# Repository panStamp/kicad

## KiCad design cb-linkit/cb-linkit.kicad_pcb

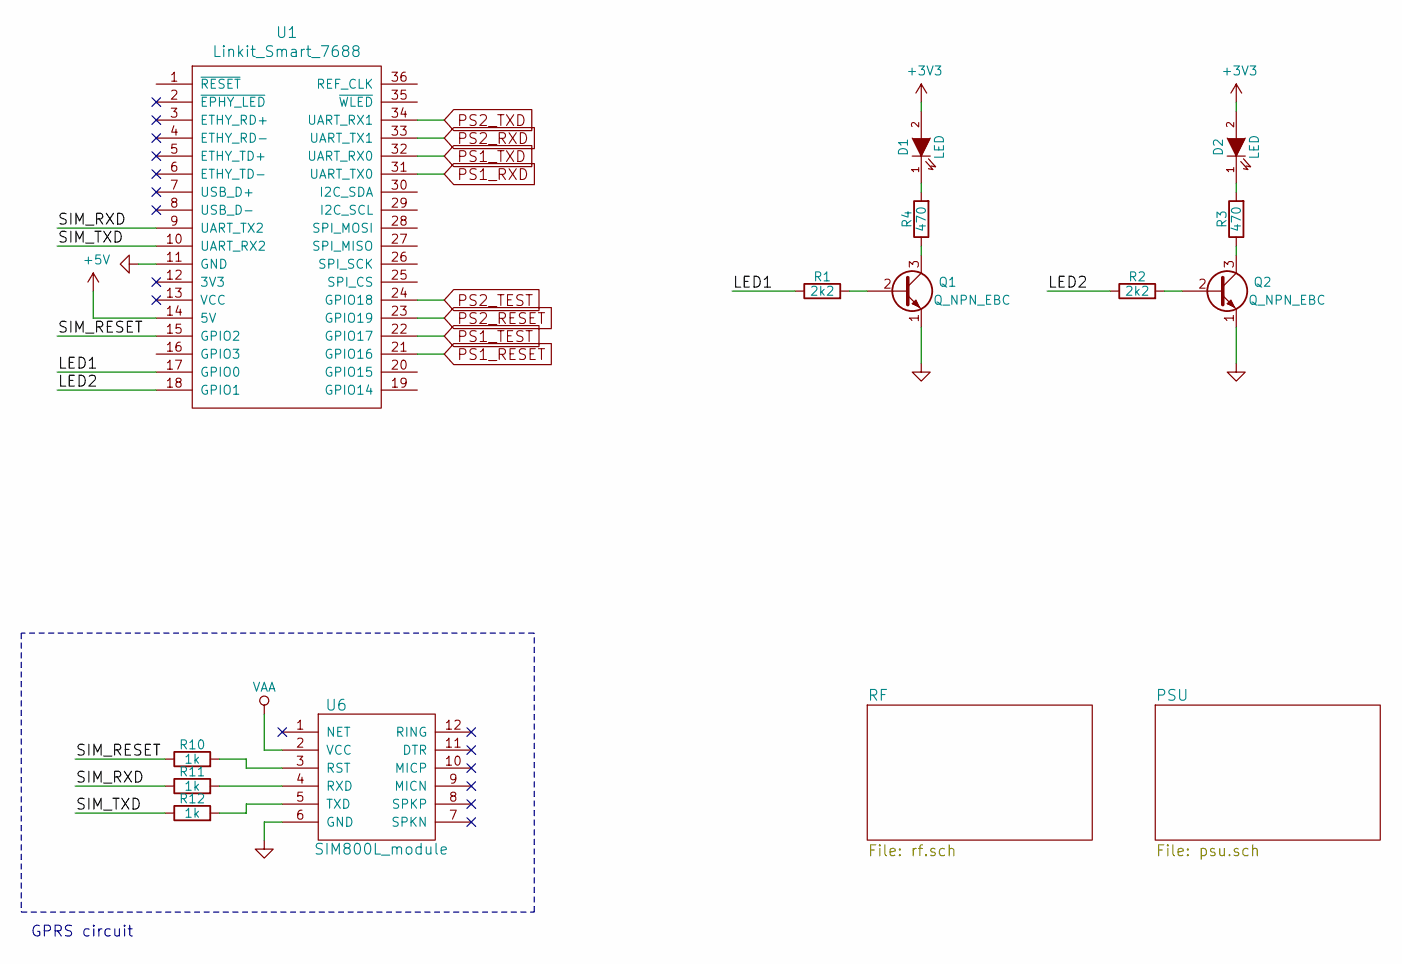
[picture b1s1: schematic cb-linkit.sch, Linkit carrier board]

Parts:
D1, D2: LED; SM0603S_POL
Q1, Q2: Q_NPN_EBC; SOT23EBC
R1, R2: 2k2; SM0603S
R3, R4: 470; SM0603S
R10, R11, R12: 1k; SM0603S
U1: Linkit_Smart_7688; DIP36-1
U6: SIM800L_module; SIM800L_MODULE

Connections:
+3V3: D1.2 (A), D2.2 (A); also elsewhere on the board
+5V: U1.14 (5V); also elsewhere on the board
/LED1: R1.1, U1.17 (GPIO0)
/LED2: R2.1, U1.18 (GPIO1)
/SIM_RESET: R10.1, U1.15 (GPIO2)
/SIM_RXD: R11.1, U1.9 (UART_TX2)
/SIM_TXD: R12.1, U1.10 (UART_RX2)
GND: Q1.1 (E), Q2.1 (E), U1.11 (GND), U6.6 (GND); also elsewhere on the board
unnamed: D1.1 (K), R4.2
unnamed: D2.1 (K), R3.2
unnamed: Q1.2 (B), R1.2
unnamed: Q1.3 (C), R4.1
unnamed: Q2.2 (B), R2.2
unnamed: Q2.3 (C), R3.1
unnamed: R10.2, U6.3 (RST)
unnamed: R11.2, U6.4 (RXD)
unnamed: R12.2, U6.5 (TXD)
PS1_RESET: U1.21 (GPIO16); also elsewhere on the board
PS1_RXD: U1.31 (UART_TX0); also elsewhere on the board
PS1_TEST: U1.22 (GPIO17); also elsewhere on the board
PS1_TXD: U1.32 (UART_RX0); also elsewhere on the board
PS2_RESET: U1.23 (GPIO19); also elsewhere on the board
PS2_RXD: U1.33 (UART_TX1); also elsewhere on the board
PS2_TEST: U1.24 (GPIO18); also elsewhere on the board
PS2_TXD: U1.34 (UART_RX1); also elsewhere on the board
VAA: U6.2 (VCC); also elsewhere on the board

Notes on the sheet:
GPRS circuit

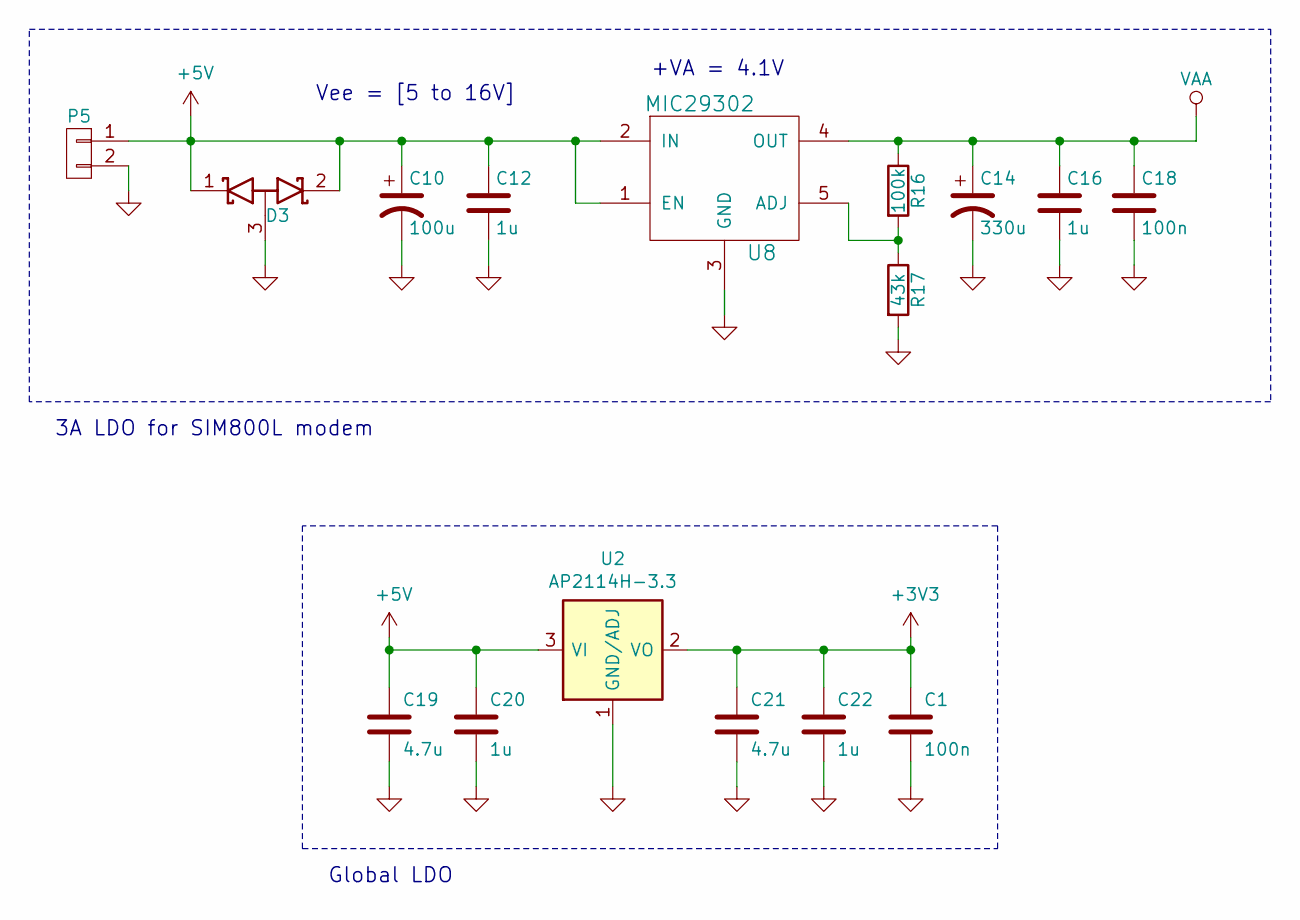
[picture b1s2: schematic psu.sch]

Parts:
C1, C18: 100n; SM0603S
C10: 100u; SMDCPOL_6.3
C12, C16, C20, C22: 1u; SM0603S
C14: 330u; SMDCPOL_8
C19, C21: 4.7u; SM0603S
D3: D_Schottky_x2_ACom_KKA; SOT23
P5: CONN_01X02; PWR_3A
R16: 100k; SM0603S
R17: 43k; SM0603S
U2: AP2114H-3.3; SOT223
U8: MIC29302; TO-252

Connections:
+3V3: C1.1, C21.1, C22.1, U2.2 (VO); also elsewhere on the board
+5V: C10.1, C12.1, C19.1, C20.1, D3.1 (K), D3.2 (K), P5.1, U2.3 (VI), U8.1 (EN), U8.2 (IN); also elsewhere on the board
GND: C1.2, C10.2, C12.2, C14.2, C16.2, C18.2, C19.2, C20.2, C21.2, C22.2, D3.3 (A), P5.2, R17.2, U2.1 (GND/ADJ), U8.3 (GND); also elsewhere on the board
unnamed: R16.2, R17.1, U8.5 (ADJ)
VAA: C14.1, C16.1, C18.1, R16.1, U8.4 (OUT); also elsewhere on the board

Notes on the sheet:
+VA = 4.1V
Vee = [5 to 16V]
3A LDO for SIM800L modem
Global LDO

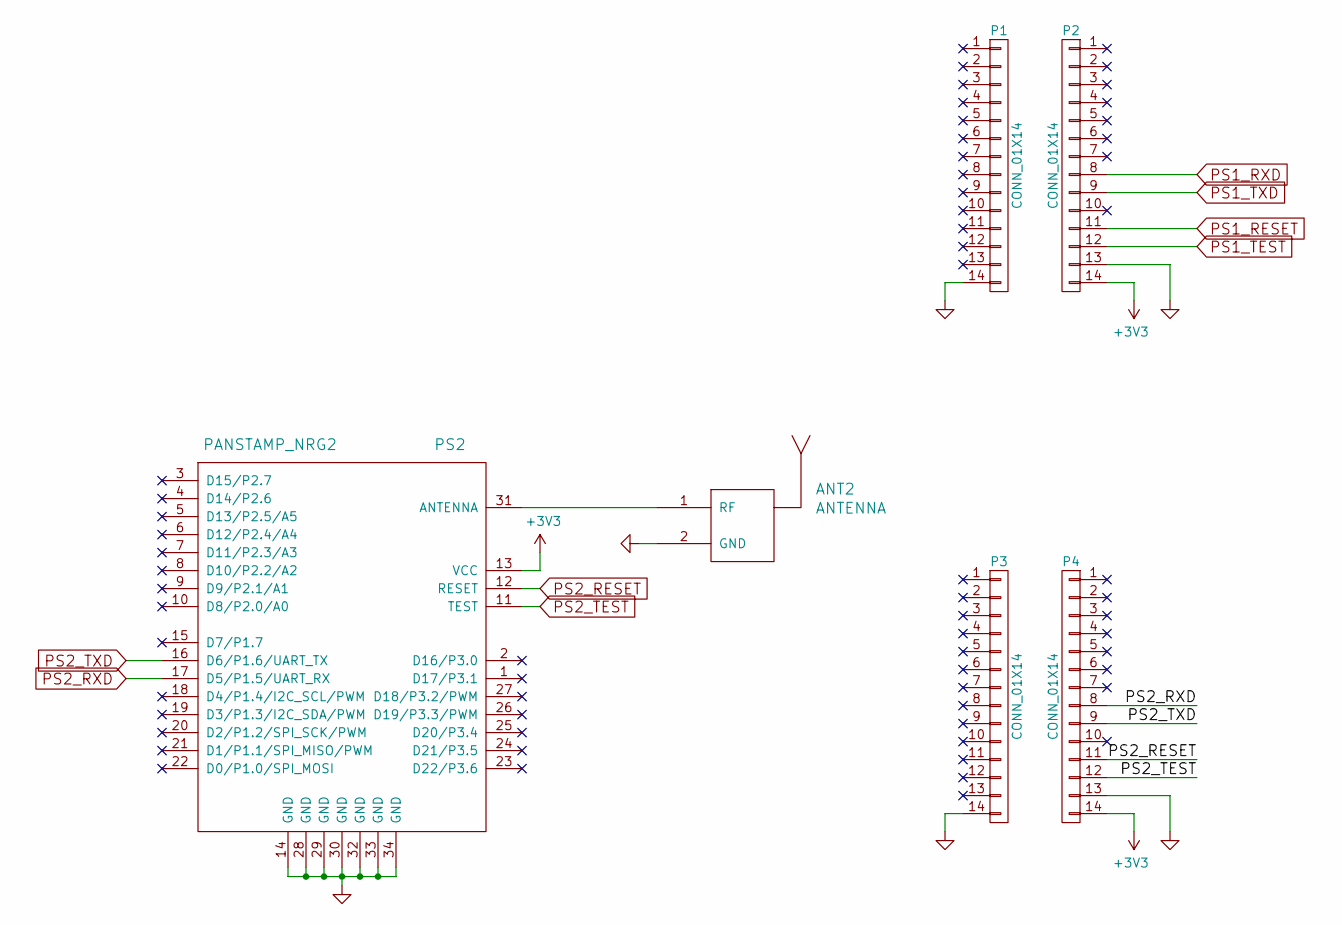
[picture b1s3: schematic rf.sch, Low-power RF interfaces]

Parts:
ANT2: ANTENNA; SMA_RightAngle_Tyco
P1, P2, P3, P4: CONN_01X14; Pin_Header_Straight_1x14
PS2: PANSTAMP_NRG2; PANSTAMP_2

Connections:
+3V3: P2.14, P4.14, PS2.13 (VCC); also elsewhere on the board
GND: ANT2.2 (GND), P1.14, P2.13, P3.14, P4.13, PS2.14 (GND), PS2.28 (GND), PS2.29 (GND), PS2.30 (GND), PS2.32 (GND), PS2.33 (GND), PS2.34 (GND); also elsewhere on the board
unnamed: ANT2.1 (RF), PS2.31 (ANTENNA)
PS1_RESET: P2.11; also elsewhere on the board
PS1_RXD: P2.8; also elsewhere on the board
PS1_TEST: P2.12; also elsewhere on the board
PS1_TXD: P2.9; also elsewhere on the board
PS2_RESET: P4.11, PS2.12 (RESET); also elsewhere on the board
PS2_RXD: P4.8, PS2.17 (D5/P1.5/UART_RX); also elsewhere on the board
PS2_TEST: P4.12, PS2.11 (TEST); also elsewhere on the board
PS2_TXD: P4.9, PS2.16 (D6/P1.6/UART_TX); also elsewhere on the board

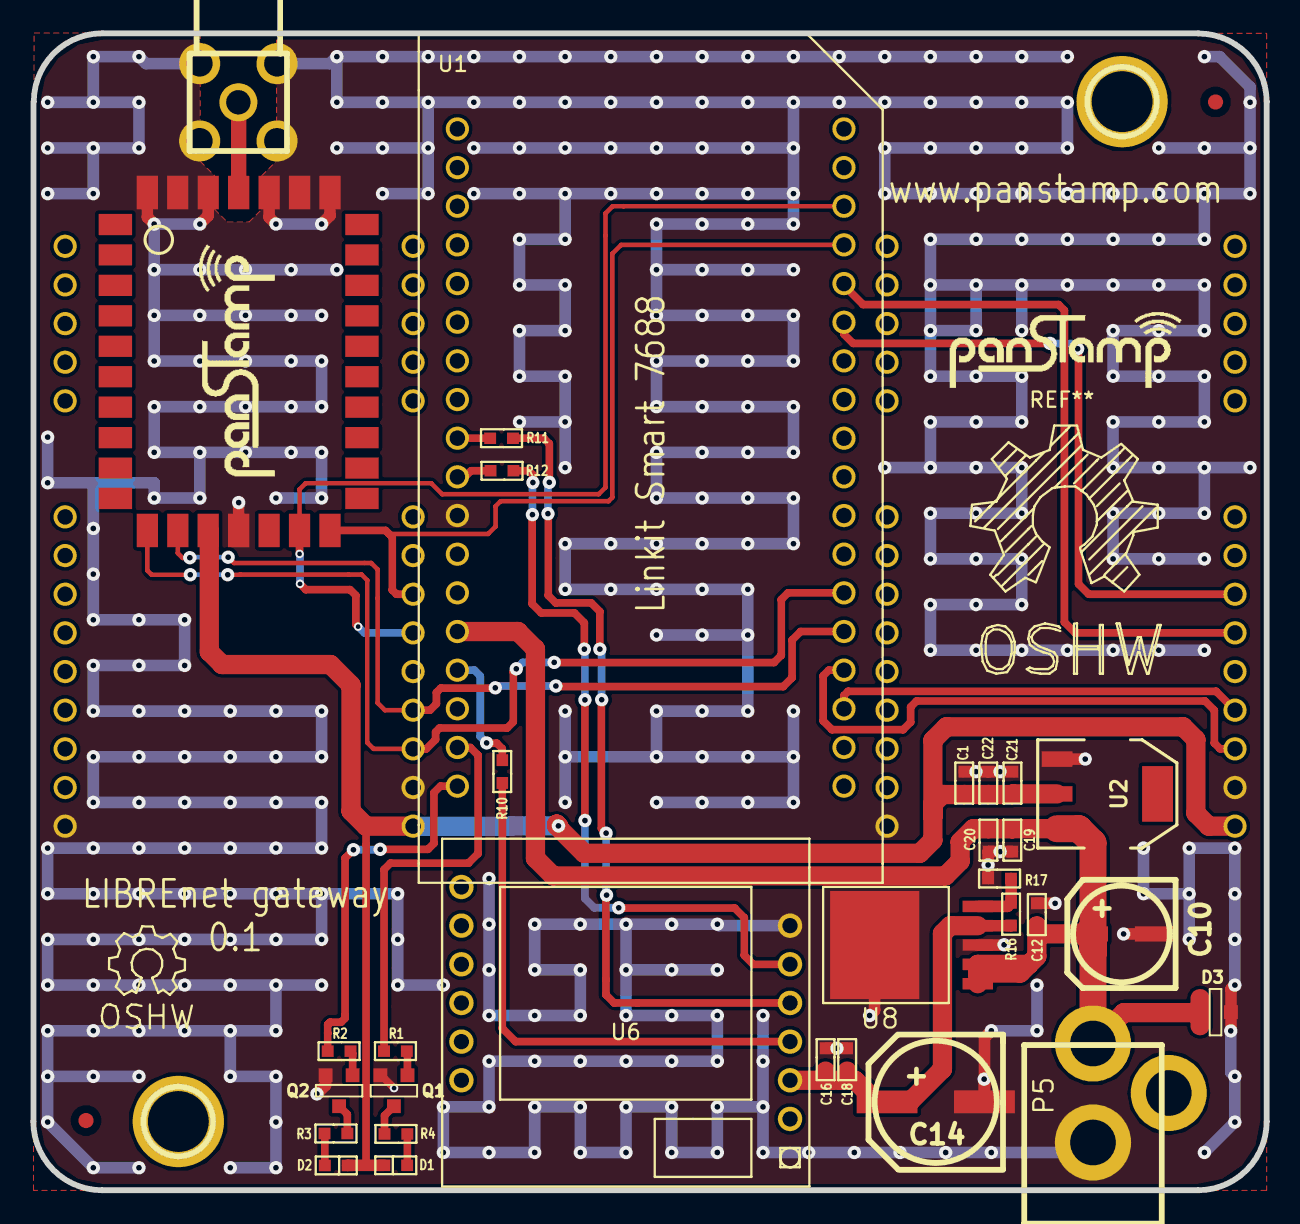
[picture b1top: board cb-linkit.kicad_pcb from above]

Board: 4 copper layers, 81.0 x 76.0 mm, 39 parts (0 on the bottom side), 28 nets.

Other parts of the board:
1PIN, 1PIN#2: P***; 1pin
fiducial: VAL**; fiducial
fiducial#2: VAL**; fiducial

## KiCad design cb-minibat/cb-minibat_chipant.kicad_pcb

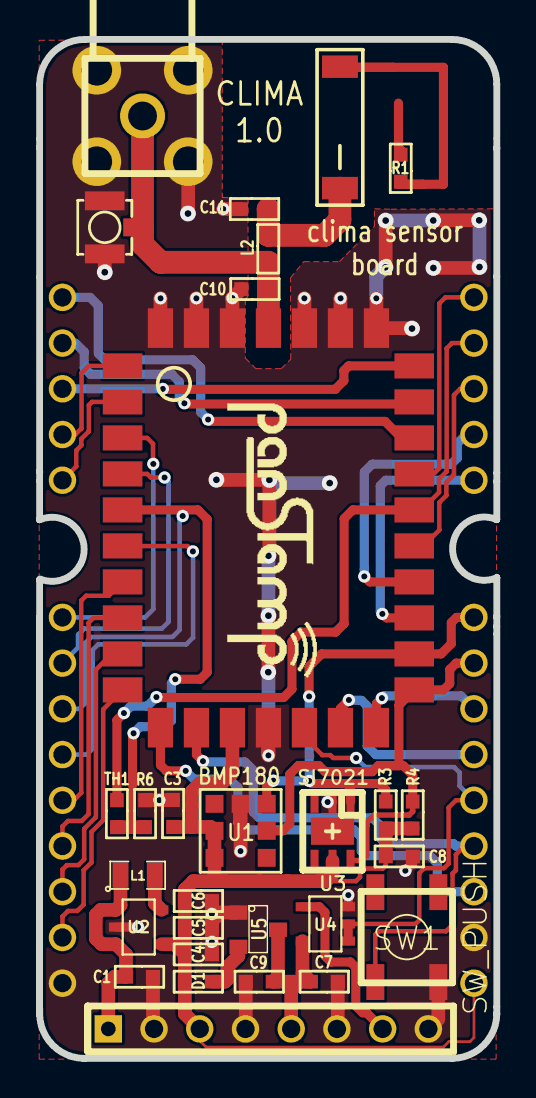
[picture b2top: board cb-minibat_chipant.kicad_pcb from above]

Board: 4 copper layers, 25.4 x 56.6 mm, 31 parts (0 on the bottom side), 35 nets.

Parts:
ANT1: ANTENNA; SMA_RightAngle_Tyco
ANT2: ANTENNA; U.FL_CONN
C1, C4, C9: 10u; SM0603S
C3, C6, C7, C8: 100n; SM0603S
C5: 1u; SM0603S
C10: 3.9p; SM0603S
C11: 0.3p; SM0603S
D1: SD0603S040S0R2; SM0603S
L1: 4.7u; SM0805
L2: 18n; SM0603S
L3: ANTENNA; 0868AT43A0020
P1, P2: CONN_01X14; pin_array_1x14
P3: CONN_8; PIN_ARRAY_8X1
PS1: PANSTAMP_NRG2; PANSTAMP_2
R1: 0; SM0603S
R3, R4, R6: 10k; SM0603S
SW1: SW_PUSH; switch-tact-noah
TH1: THERMISTOR; SM0603S
U1: BMP180
U2: MAX1724; SOT23-5
U3: SI7021; DFN-6
U4: M74VHC1GT08; SOT23-5
U5: MCP1702; SOT23

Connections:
+5V: C7.1, C9.1, P3.5, U4.5, U5.3
+BATT: C1.1, L1.1, P3.1, U2.1, U2.3
/5VOUT: P3.7, U4.4
/A5: P1.8, PS1.5, R6.1, TH1.1
/CHIP_ANT: C11.1, L2.2, L3.1
/D0: P2.3, PS1.22
/D1: P2.4, PS1.21
/D2: P2.5, PS1.20
/D5: P2.8, PS1.17
/D6: P2.9, PS1.16
/D7: P2.10, PS1.15, U4.1, U4.2
/D8: P1.13, PS1.10
/D9: P1.12, PS1.9
/D10: P1.11, PS1.8
/D11: P1.10, PS1.7
/D12: P1.9, PS1.6
/D14: P1.7, PS1.4
/D15: P1.6, PS1.3
/D16: P1.5, PS1.2
/D17: P1.4, PS1.1
/D18: P1.3, PS1.27
/D19: P1.2, PS1.26
/D20: P1.1, PS1.25
/D21: P2.1, PS1.24
/D22: P2.2, PS1.23, TH1.2
/I2C_SCL: P2.7, PS1.18, R4.2, U1.5, U3.6
/I2C_SDA: P2.6, PS1.19, R3.2, U1.6, U3.1
/RESET: P2.11, PS1.12, SW1.1
/TEST: P2.12, PS1.11
/TOANT: ANT1.1, ANT2.1, C10.1, L2.1, PS1.31
GND: ANT1.2, ANT2.2, C1.2, C3.2, C4.2, C5.2, C6.2, C7.2, C8.2, C9.2, C10.2, C11.2, P1.14, P2.13, P3.2, P3.4, P3.6, P3.8, PS1.14, PS1.28, PS1.29, PS1.30, PS1.32, PS1.33, PS1.34, R6.2, SW1.2, U1.7, U2.2, U3.2, U4.3, U5.1
unnamed: D1.1, U5.2
unnamed: L1.2, U2.5
unnamed: L3.2, R1.2
VCC: C3.1, C4.1, C5.1, C6.1, C8.1, D1.2, P2.14, P3.3, PS1.13, R3.1, R4.1, U1.2, U1.3, U2.4, U3.5

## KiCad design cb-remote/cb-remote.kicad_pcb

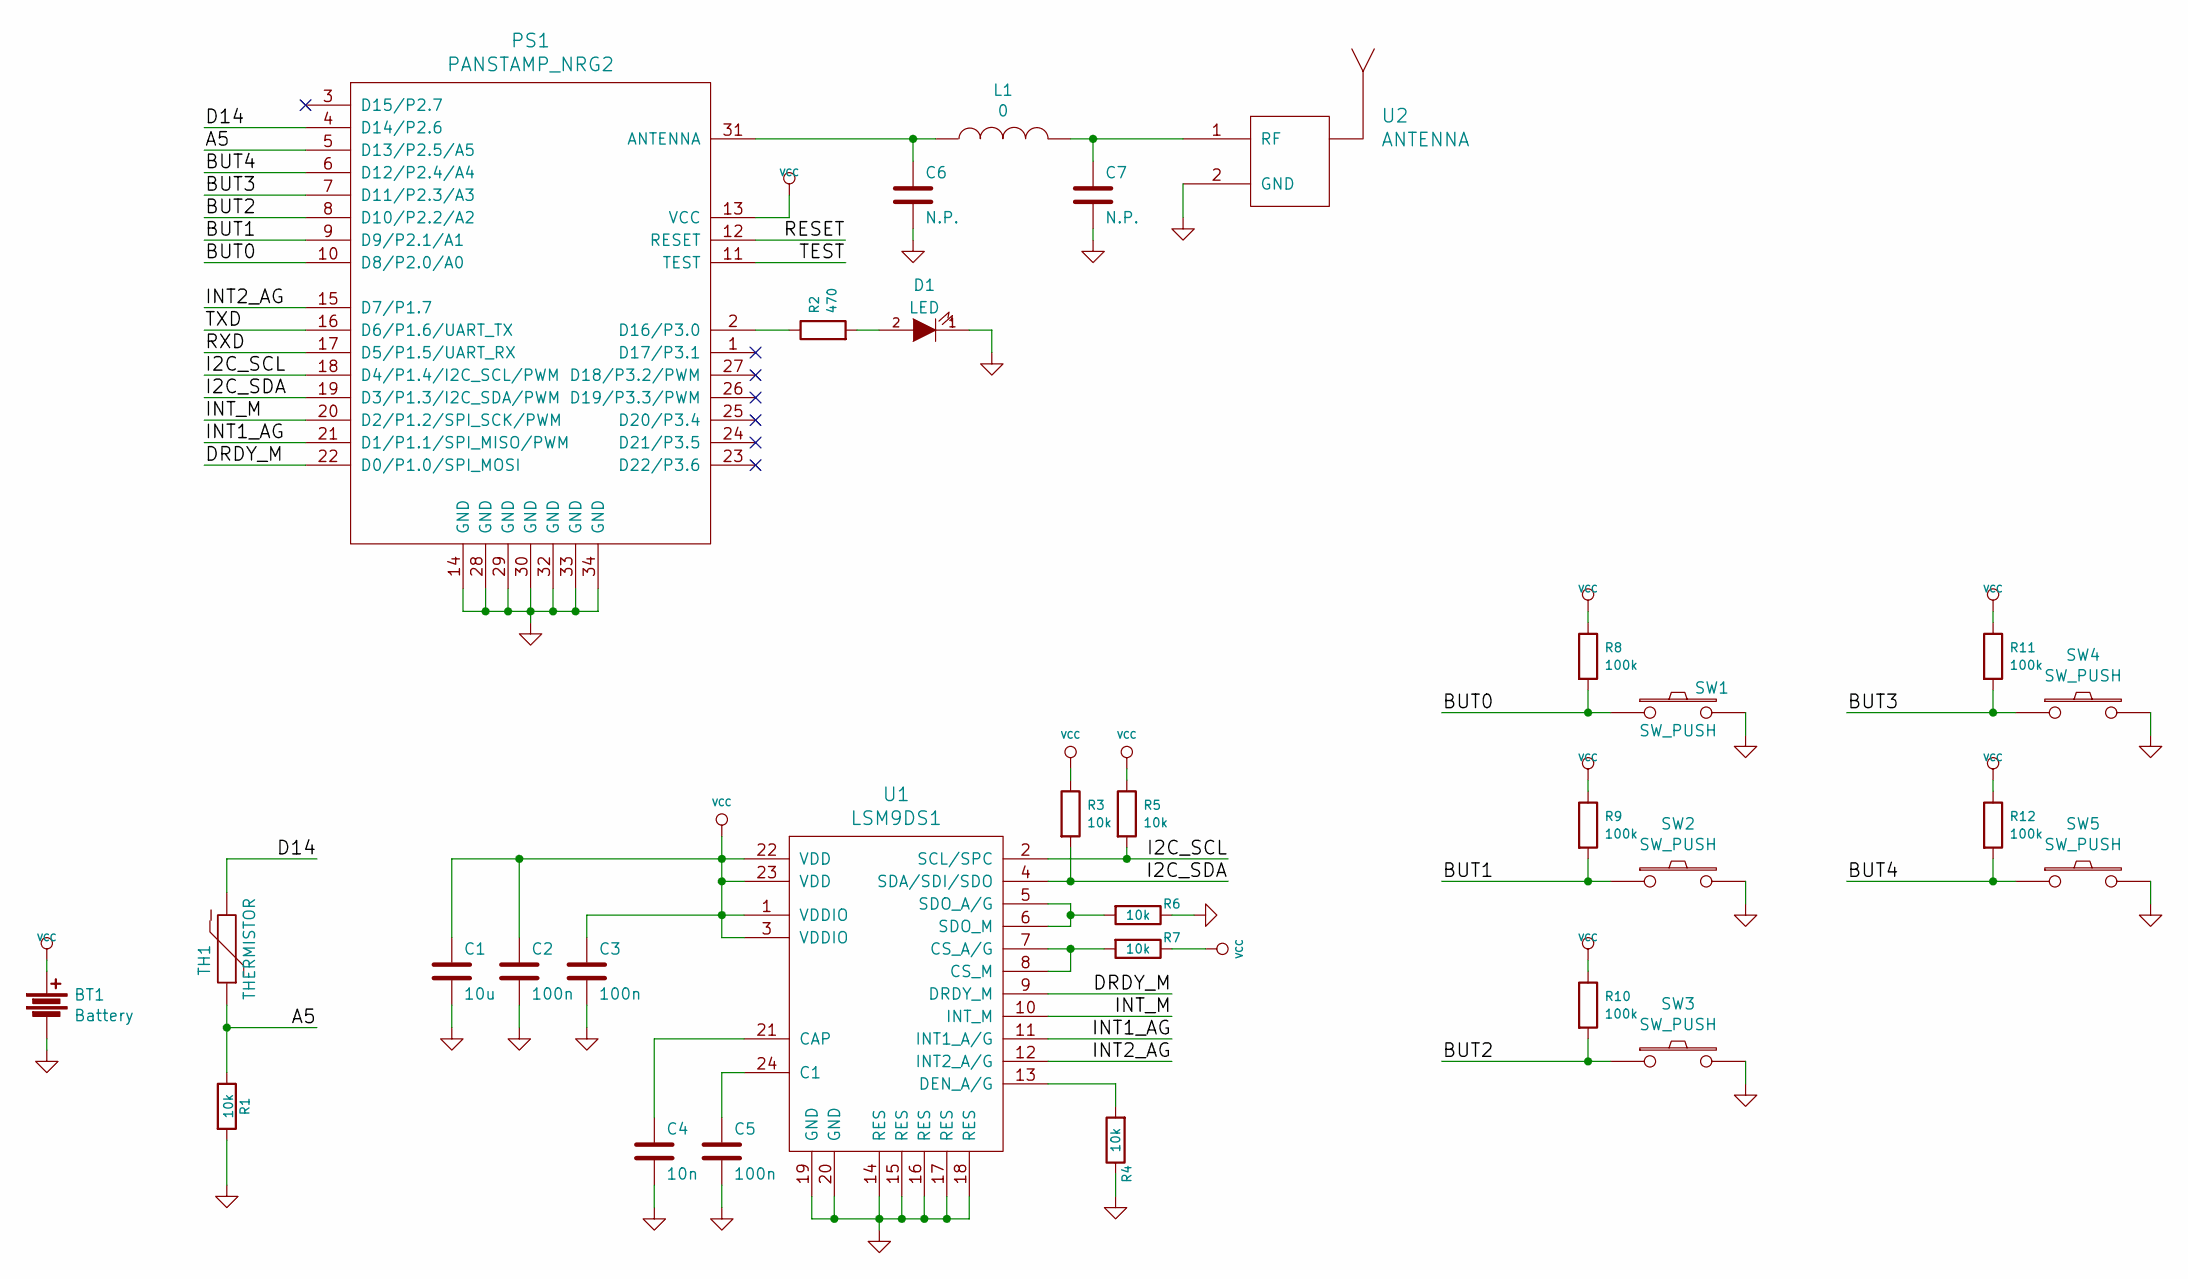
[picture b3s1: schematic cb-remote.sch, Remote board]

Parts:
BT1: Battery; linx_bat-hld-001
C1: 10u; SM0603S
C2, C3, C5: 100n; SM0603S
C4: 10n; SM0603S
C6, C7: N.P.; SM0603S
D1: LED; SM0603_POL
L1: 0; SM0603S
PS1: PANSTAMP_NRG2; PANSTAMP_2
R1, R3, R4, R5, R6, R7: 10k; SM0603S
R2: 470; SM0603S
R8, R9, R10, R11, R12: 100k; SM0603S
SW1, SW2, SW3, SW4, SW5: SW_PUSH; minimum_jumper
TH1: THERMISTOR; SM0603S
U1: LSM9DS1; LGA24L
U2: ANTENNA; U.FL_CONN

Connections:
/A5: PS1.5 (D13/P2.5/A5), R1.1, TH1.1
/BUT0: PS1.10 (D8/P2.0/A0), R8.2, SW1.1
/BUT1: PS1.9 (D9/P2.1/A1), R9.2, SW2.1
/BUT2: PS1.8 (D10/P2.2/A2), R10.2, SW3.1
/BUT3: PS1.7 (D11/P2.3/A3), R11.2, SW4.1
/BUT4: PS1.6 (D12/P2.4/A4), R12.2, SW5.1
/D14: PS1.4 (D14/P2.6), TH1.2
/DRDY_M: PS1.22 (D0/P1.0/SPI_MOSI), U1.9 (DRDY_M)
/I2C_SCL: PS1.18 (D4/P1.4/I2C_SCL/PWM), R5.2, U1.2 (SCL/SPC)
/I2C_SDA: PS1.19 (D3/P1.3/I2C_SDA/PWM), R3.2, U1.4 (SDA/SDI/SDO)
/INT1_AG: PS1.21 (D1/P1.1/SPI_MISO/PWM), U1.11 (INT1_A/G)
/INT2_AG: PS1.15 (D7/P1.7), U1.12 (INT2_A/G)
/INT_M: PS1.20 (D2/P1.2/SPI_SCK/PWM), U1.10 (INT_M)
/RESET: PS1.12 (RESET)
/RXD: PS1.17 (D5/P1.5/UART_RX)
/TEST: PS1.11 (TEST)
/TXD: PS1.16 (D6/P1.6/UART_TX)
GND: BT1.2, C1.2, C2.2, C3.2, C4.2, C5.2, C6.2, C7.2, D1.1 (K), PS1.14 (GND), PS1.28 (GND), PS1.29 (GND), PS1.30 (GND), PS1.32 (GND), PS1.33 (GND), PS1.34 (GND), R1.2, R4.1, R6.1, SW1.2, SW2.2, SW3.2, SW4.2, SW5.2, U1.14 (RES), U1.15 (RES), U1.16 (RES), U1.17 (RES), U1.18 (RES), U1.19 (GND), U1.20 (GND), U2.2 (GND)
unnamed: C4.1, U1.21 (CAP)
unnamed: C5.1, U1.24 (C1)
unnamed: C6.1, L1.1, PS1.31 (ANTENNA)
unnamed: C7.1, L1.2, U2.1 (RF)
unnamed: D1.2 (A), R2.2
unnamed: PS1.2 (D16/P3.0), R2.1
unnamed: R4.2, U1.13 (DEN_A/G)
unnamed: R6.2, U1.5 (SDO_A/G), U1.6 (SDO_M)
unnamed: R7.2, U1.7 (CS_A/G), U1.8 (CS_M)
VCC: BT1.1, C1.1, C2.1, C3.1, PS1.13 (VCC), R3.1, R5.1, R7.1, R8.1, R9.1, R10.1, R11.1, R12.1, U1.1 (VDDIO), U1.3 (VDDIO), U1.22 (VDD), U1.23 (VDD)

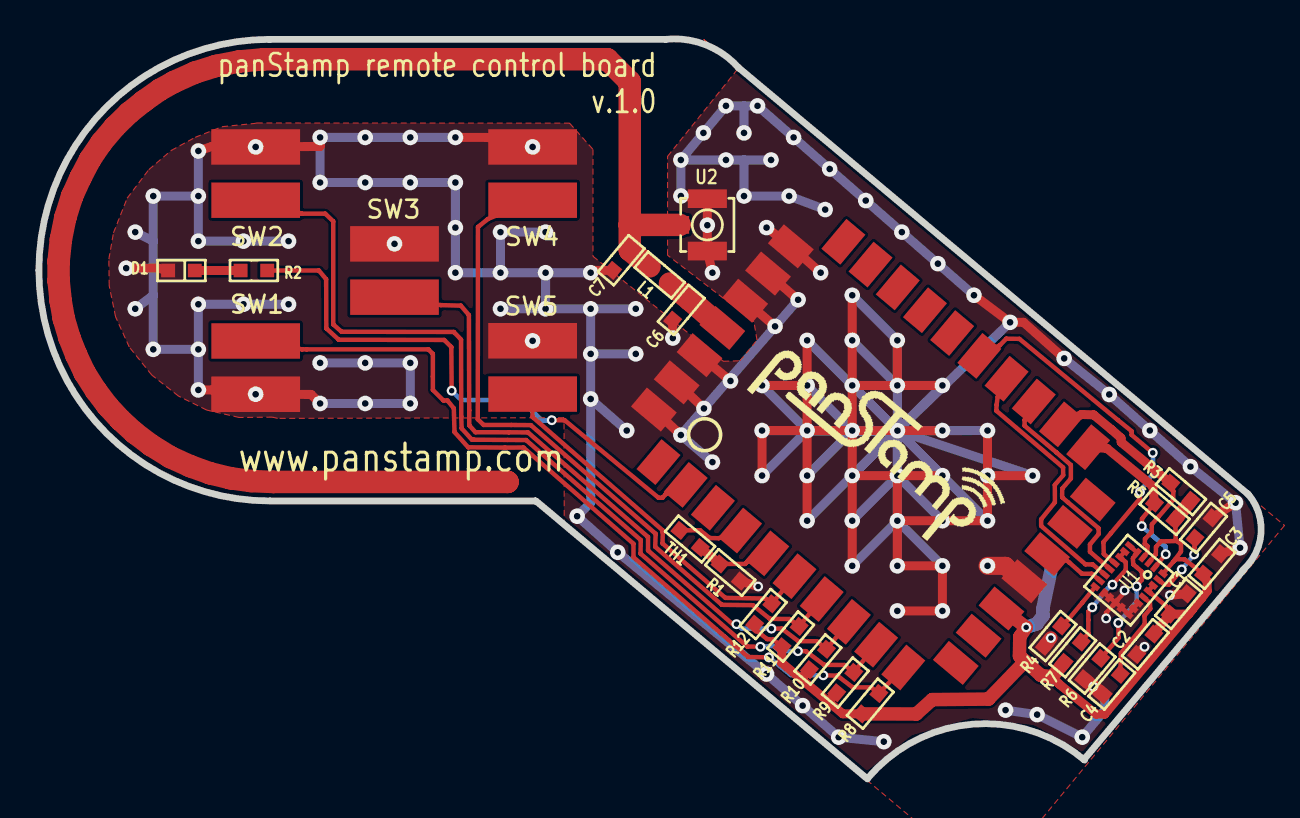
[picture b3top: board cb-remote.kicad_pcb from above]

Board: 4 copper layers, 68.8 x 41.7 mm, 31 parts (1 on the bottom side), 24 nets.

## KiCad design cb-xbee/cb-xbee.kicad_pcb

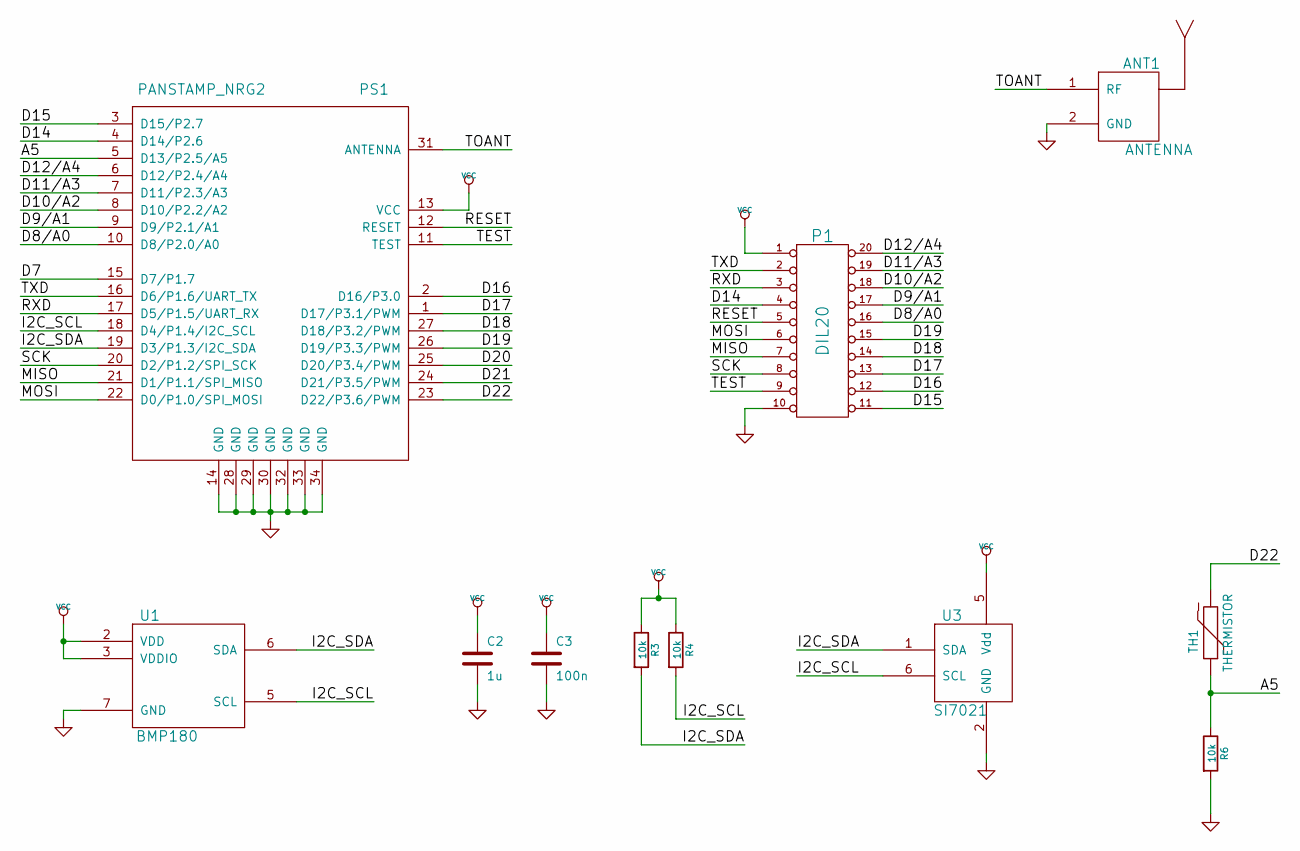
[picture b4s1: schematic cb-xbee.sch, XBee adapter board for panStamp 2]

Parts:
ANT1: ANTENNA; SMA_RightAngle_Tyco
C2: 1u; SM0603S
C3: 100n; SM0603S
P1: DIL20
PS1: PANSTAMP_NRG2; PANSTAMP_2
R3, R4, R6: 10k; SM0603S
TH1: THERMISTOR; SM0603S
U1: BMP180
U3: SI7021; DFN-6

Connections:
/A5: PS1.5 (D13/P2.5/A5), R6.1, TH1.1
/D7: PS1.15 (D7/P1.7)
/D8/A0: P1.16, PS1.10 (D8/P2.0/A0)
/D9/A1: P1.17, PS1.9 (D9/P2.1/A1)
/D10/A2: P1.18, PS1.8 (D10/P2.2/A2)
/D11/A3: P1.19, PS1.7 (D11/P2.3/A3)
/D12/A4: P1.20, PS1.6 (D12/P2.4/A4)
/D14: P1.4, PS1.4 (D14/P2.6)
/D15: P1.11, PS1.3 (D15/P2.7)
/D16: P1.12, PS1.2 (D16/P3.0)
/D17: P1.13, PS1.1 (D17/P3.1/PWM)
/D18: P1.14, PS1.27 (D18/P3.2/PWM)
/D19: P1.15, PS1.26 (D19/P3.3/PWM)
/D20: PS1.25 (D20/P3.4/PWM)
/D21: PS1.24 (D21/P3.5/PWM)
/D22: PS1.23 (D22/P3.6/PWM), TH1.2
/I2C_SCL: PS1.18 (D4/P1.4/I2C_SCL), R4.2, U1.5 (SCL), U3.6 (SCL)
/I2C_SDA: PS1.19 (D3/P1.3/I2C_SDA), R3.2, U1.6 (SDA), U3.1 (SDA)
/MISO: P1.7, PS1.21 (D1/P1.1/SPI_MISO)
/MOSI: P1.6, PS1.22 (D0/P1.0/SPI_MOSI)
/RESET: P1.5, PS1.12 (RESET)
/RXD: P1.3, PS1.17 (D5/P1.5/UART_RX)
/SCK: P1.8, PS1.20 (D2/P1.2/SPI_SCK)
/TEST: P1.9, PS1.11 (TEST)
/TOANT: ANT1.1 (RF), PS1.31 (ANTENNA)
/TXD: P1.2, PS1.16 (D6/P1.6/UART_TX)
GND: ANT1.2 (GND), C2.2, C3.2, P1.10, PS1.14 (GND), PS1.28 (GND), PS1.29 (GND), PS1.30 (GND), PS1.32 (GND), PS1.33 (GND), PS1.34 (GND), R6.2, U1.7 (GND), U3.2 (GND)
VCC: C2.1, C3.1, P1.1, PS1.13 (VCC), R3.1, R4.1, U1.2 (VDD), U1.3 (VDDIO), U3.5 (Vdd)

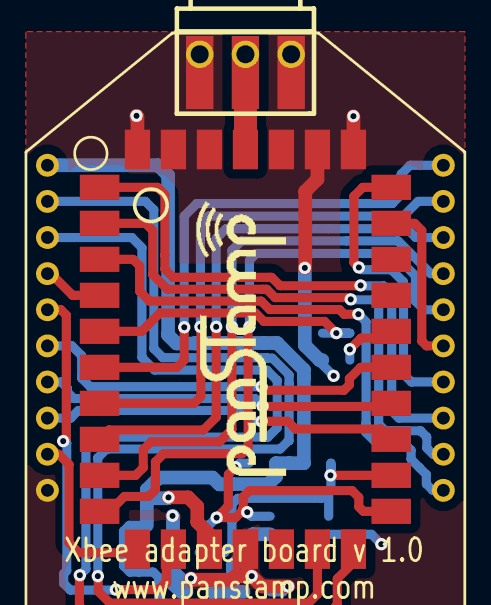
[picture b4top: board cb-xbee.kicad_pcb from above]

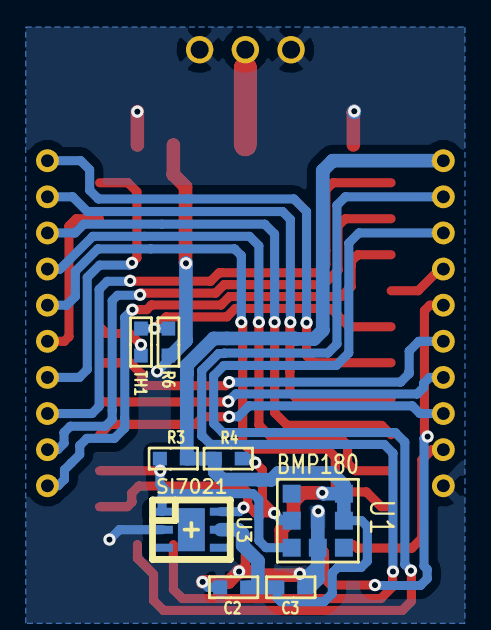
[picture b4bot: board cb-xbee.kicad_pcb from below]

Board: 4 copper layers, 11 parts (8 on the bottom side), 25 nets.

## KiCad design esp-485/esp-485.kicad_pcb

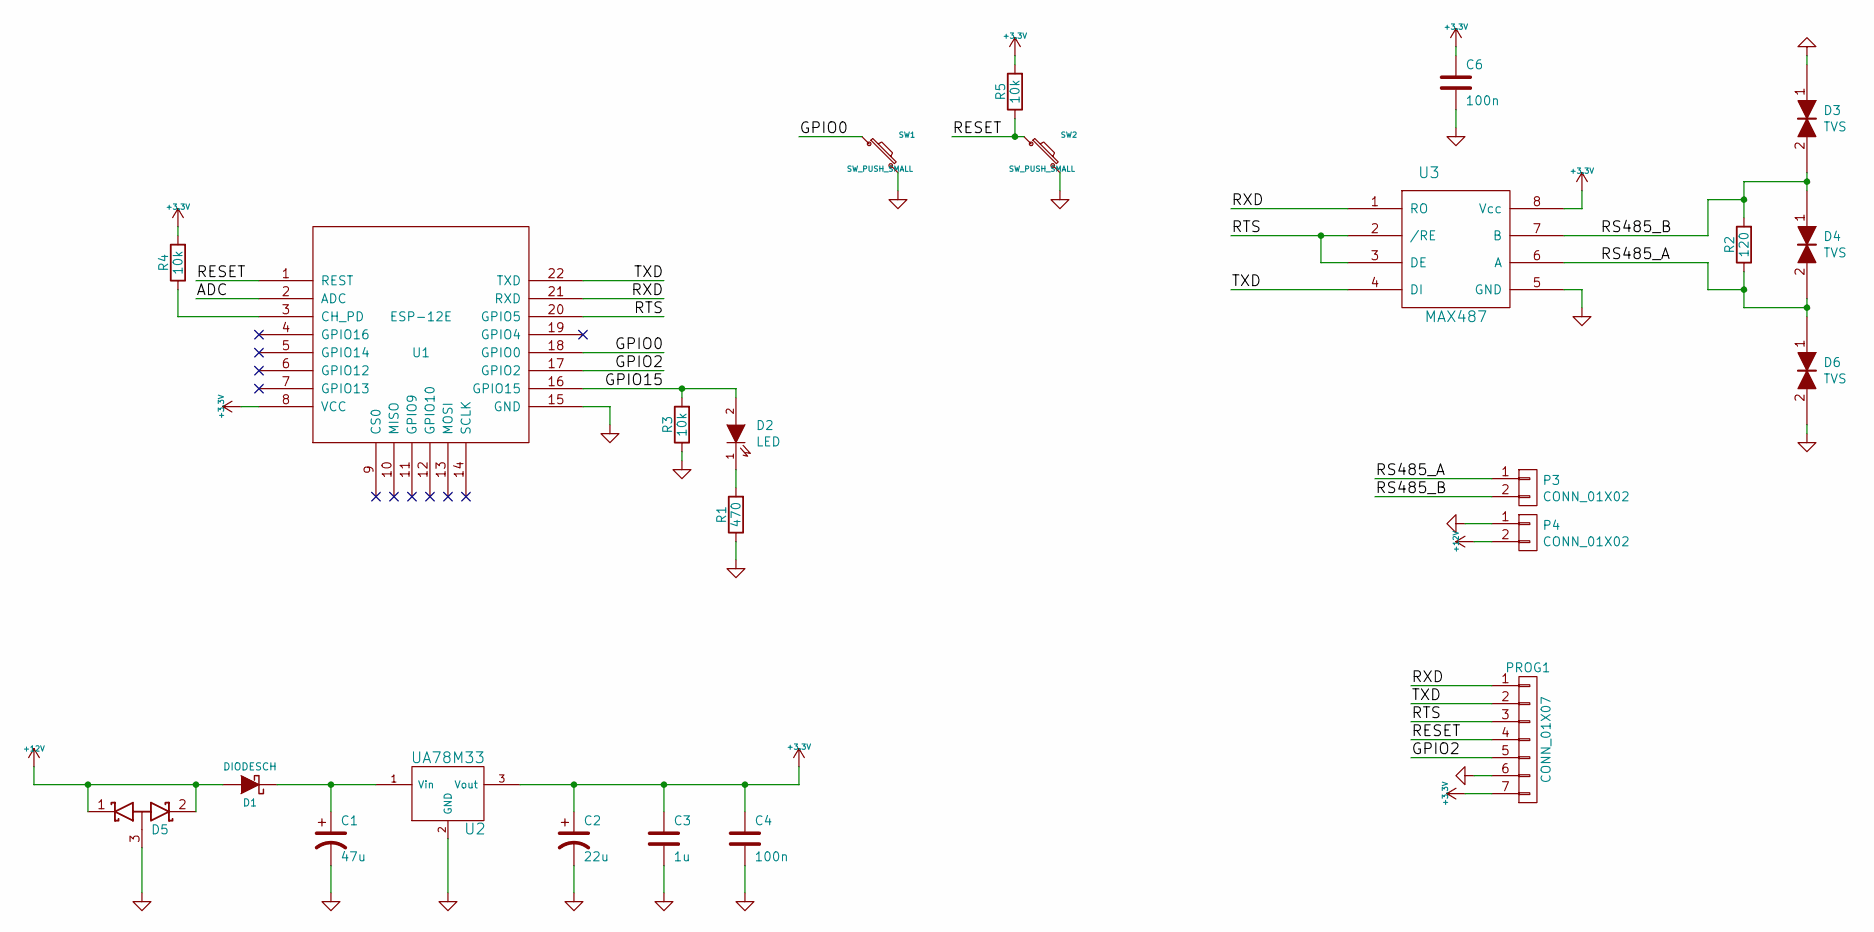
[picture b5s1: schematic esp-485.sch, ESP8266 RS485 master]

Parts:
C1: 47u; SMDCPOL_6.3
C2: 22u; SMDCPOL_5
C3: 1u; SM0603S
C4, C6: 100n; SM0603S
D1: DIODESCH; SMA
D2: LED; SM0603S_POL
D3, D4, D6: TVS; SOD-923
D5: D_Schottky_x2_ACom_KKA; SOT23
P3, P4: CONN_01X02; terminal_block_5mm_2P
PROG1: CONN_01X07; Pin_Header_Straight_1x07
R1: 470; SM0603S
R2: 120; SM0603S
R3, R4, R5: 10k; SM0603S
SW1, SW2: SW_PUSH_SMALL; switch-tact-noah
U1: ESP-12E
U2: UA78M33; SOT223
U3: MAX487; SO8E

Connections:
+3V3: C2.1, C3.1, C4.1, C6.1, PROG1.7, R4.2, R5.2, U1.8 (VCC), U2.3 (Vout), U3.8 (Vcc)
+12V: D1.2 (A), D5.1 (K), D5.2 (K), P4.2
/ADC: U1.2 (ADC)
/GPIO0: SW1.1, U1.18 (GPIO0)
/GPIO2: PROG1.5, U1.17 (GPIO2)
/GPIO15: D2.2 (A), R3.2, U1.16 (GPIO15)
/RESET: PROG1.4, R5.1, SW2.1, U1.1 (REST)
/RS485_A: D4.2, D6.1, P3.1, R2.1, U3.6 (A)
/RS485_B: D3.2, D4.1, P3.2, R2.2, U3.7 (B)
/RTS: PROG1.3, U1.20 (GPIO5), U3.2 (/RE), U3.3 (DE)
/RXD: PROG1.1, U1.21 (RXD), U3.1 (RO)
/TXD: PROG1.2, U1.22 (TXD), U3.4 (DI)
GND: C1.2, C2.2, C3.2, C4.2, C6.2, D3.1, D5.3 (A), D6.2, P4.1, PROG1.6, R1.1, R3.1, SW1.2, SW2.2, U1.15 (GND), U2.2 (GND), U2.4, U3.5 (GND)
unnamed: C1.1, D1.1 (K), U2.1 (Vin)
unnamed: D2.1 (K), R1.2
unnamed: R4.1, U1.3 (CH_PD)

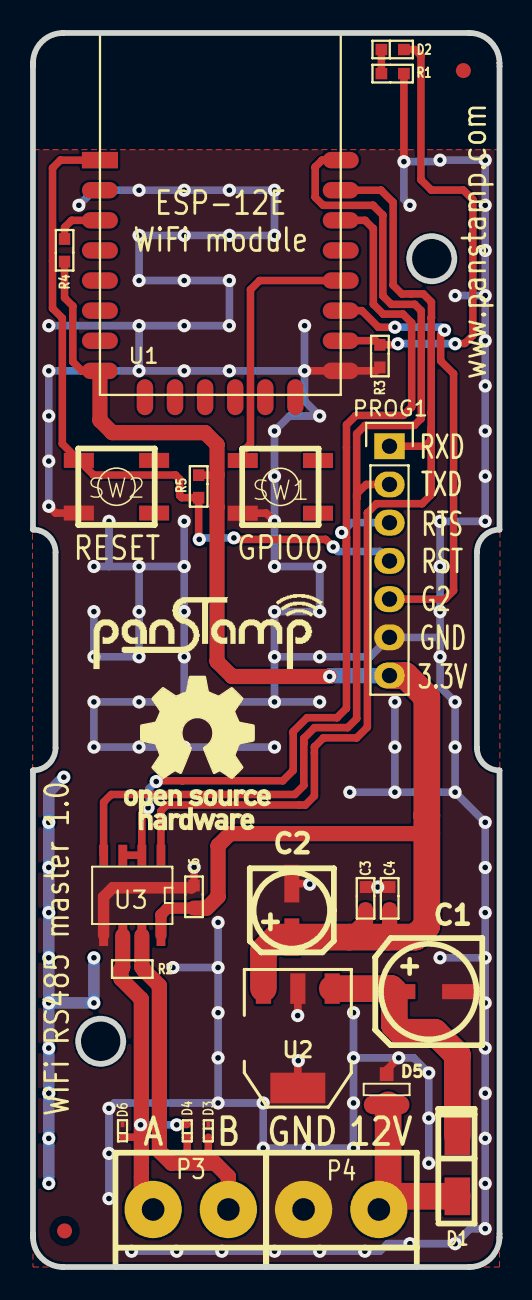
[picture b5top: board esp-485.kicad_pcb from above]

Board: 4 copper layers, 31.0 x 82.0 mm, 26 parts (0 on the bottom side), 15 nets.

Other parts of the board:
fiducial: VAL**; fiducial
fiducial#2: VAL**; fiducial

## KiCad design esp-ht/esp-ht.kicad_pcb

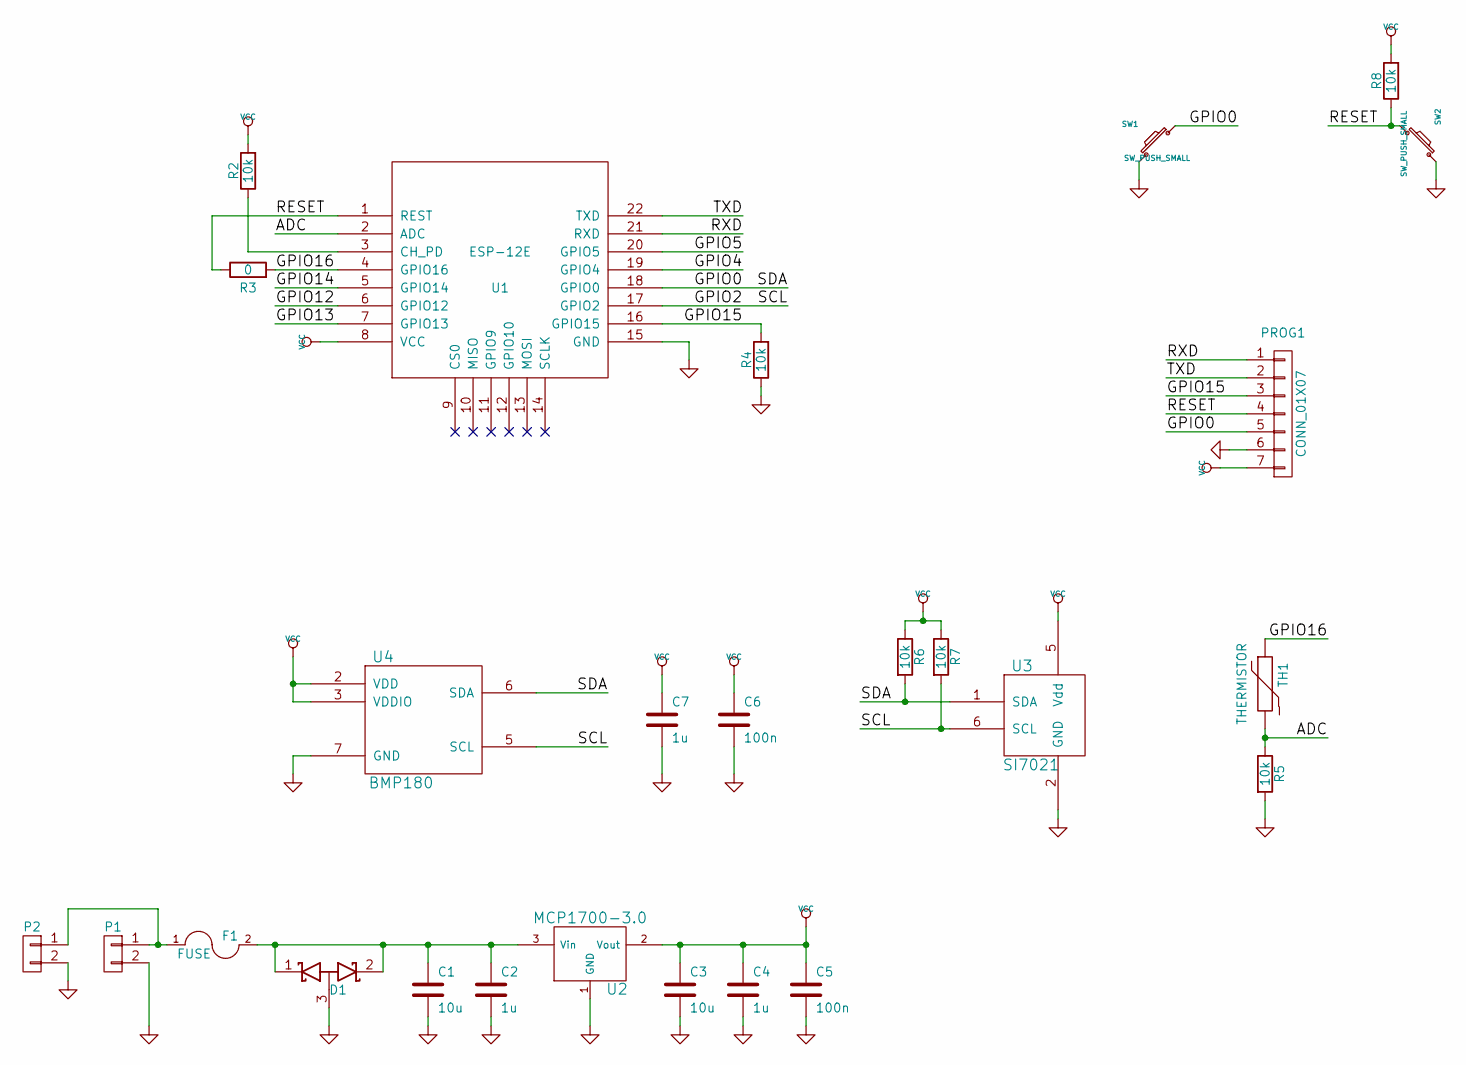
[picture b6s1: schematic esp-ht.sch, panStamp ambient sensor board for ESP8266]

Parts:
C1, C3: 10u; SM0603S
C2, C4, C7: 1u; SM0603S
C5, C6: 100n; SM0603S
D1: D_Schottky_x2_ACom_KKA; SOT23
F1: FUSE; SM0805
P1: CONN_01X02; terminal_block_5mm_2P
P2: CONN_01X02; pinhead-1-1X02
PROG1: CONN_01X07; pinhead-1-1X07
R2, R4, R5, R6, R7, R8: 10k; SM0603S
R3: 0; SM0603S
SW1, SW2: SW_PUSH_SMALL; switch-tact-noah
TH1: THERMISTOR; SM0603S
U1: ESP-12E
U2: MCP1700-3.0; SOT23
U3: SI7021; DFN-6
U4: BMP180

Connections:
/ADC: R5.1, TH1.2, U1.2 (ADC)
/GPIO0: PROG1.5, R6.2, SW1.1, U1.18 (GPIO0), U3.1 (SDA), U4.6 (SDA)
/GPIO2: R7.2, U1.17 (GPIO2), U3.6 (SCL), U4.5 (SCL)
/GPIO4: U1.19 (GPIO4)
/GPIO5: U1.20 (GPIO5)
/GPIO12: U1.6 (GPIO12)
/GPIO13: U1.7 (GPIO13)
/GPIO14: U1.5 (GPIO14)
/GPIO15: PROG1.3, R4.2, U1.16 (GPIO15)
/GPIO16: R3.2, TH1.1, U1.4 (GPIO16)
/RESET: PROG1.4, R3.1, R8.1, SW2.2, U1.1 (REST)
/RXD: PROG1.1, U1.21 (RXD)
/TXD: PROG1.2, U1.22 (TXD)
GND: C1.2, C2.2, C3.2, C4.2, C5.2, C6.2, C7.2, D1.3 (A), P1.2, P2.2, PROG1.6, R4.1, R5.2, SW1.2, SW2.1, U1.15 (GND), U2.1 (GND), U3.2 (GND), U4.7 (GND)
unnamed: C1.1, C2.1, D1.1 (K), D1.2 (K), F1.2, U2.3 (Vin)
unnamed: F1.1, P1.1, P2.1
unnamed: R2.1, U1.3 (CH_PD)
VCC: C3.1, C4.1, C5.1, C6.1, C7.1, PROG1.7, R2.2, R6.1, R7.1, R8.2, U1.8 (VCC), U2.2 (Vout), U3.5 (Vdd), U4.2 (VDD), U4.3 (VDDIO)
